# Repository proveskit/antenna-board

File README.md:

# antenna-board

This repo contains the KiCAD files for the PROVES Kit Antenna Board. This board currently goes on the +Z endcap of the satellite and hosts the antennas, interfacing ports, and some other support circuitry!

## antenna_top_cap_board_v1a
This antenna board is a reformat of the V1 Antenna Board that consolidates a bunch of the 2pos Picolock and STEMMA connectors into a single connector that runs back to the V3b EPS Board. We are probably going to leapfrog this version to land on V2 which fundementally changes things about the antenna feed path. 

## antenna_top_cap_v2
This version of the antenna top cap featuers major changes to the antenna feed path and debug passthroughs. Notable features are as follows: 
- Updated Balun Part Number (no longer sucks! still sucks to solder though)
- Addition of 12-pos and 5-pos Battery Board and Flight Controller Board debug connectors.

## antenna_top_cap_v2d
V2c plus USB charging and an SWD pass-through. See `antenna_top_cap_v2d/DECISIONS.md` for the design calls and ATP lines.
- BQ25886 2S boost charger on a new charge-only USB-C (J204), 5 V only (no PD negotiation), up to 1 A into the pack, 8.2 V float. J12 "FC USB" stays data-only.
- 1.5 A fuse plus a 0 Ohm "CHG LINK" (R210, outer face) between the charger and the battery. Hot-air R210 off before flight.
- Green LED: USB 5 V present. Red LED: charging (blinks on a fault).
- J201 (inner face) to J202 (outer face) JST-SH SWD pass-through, same pinout as the FC's J22.

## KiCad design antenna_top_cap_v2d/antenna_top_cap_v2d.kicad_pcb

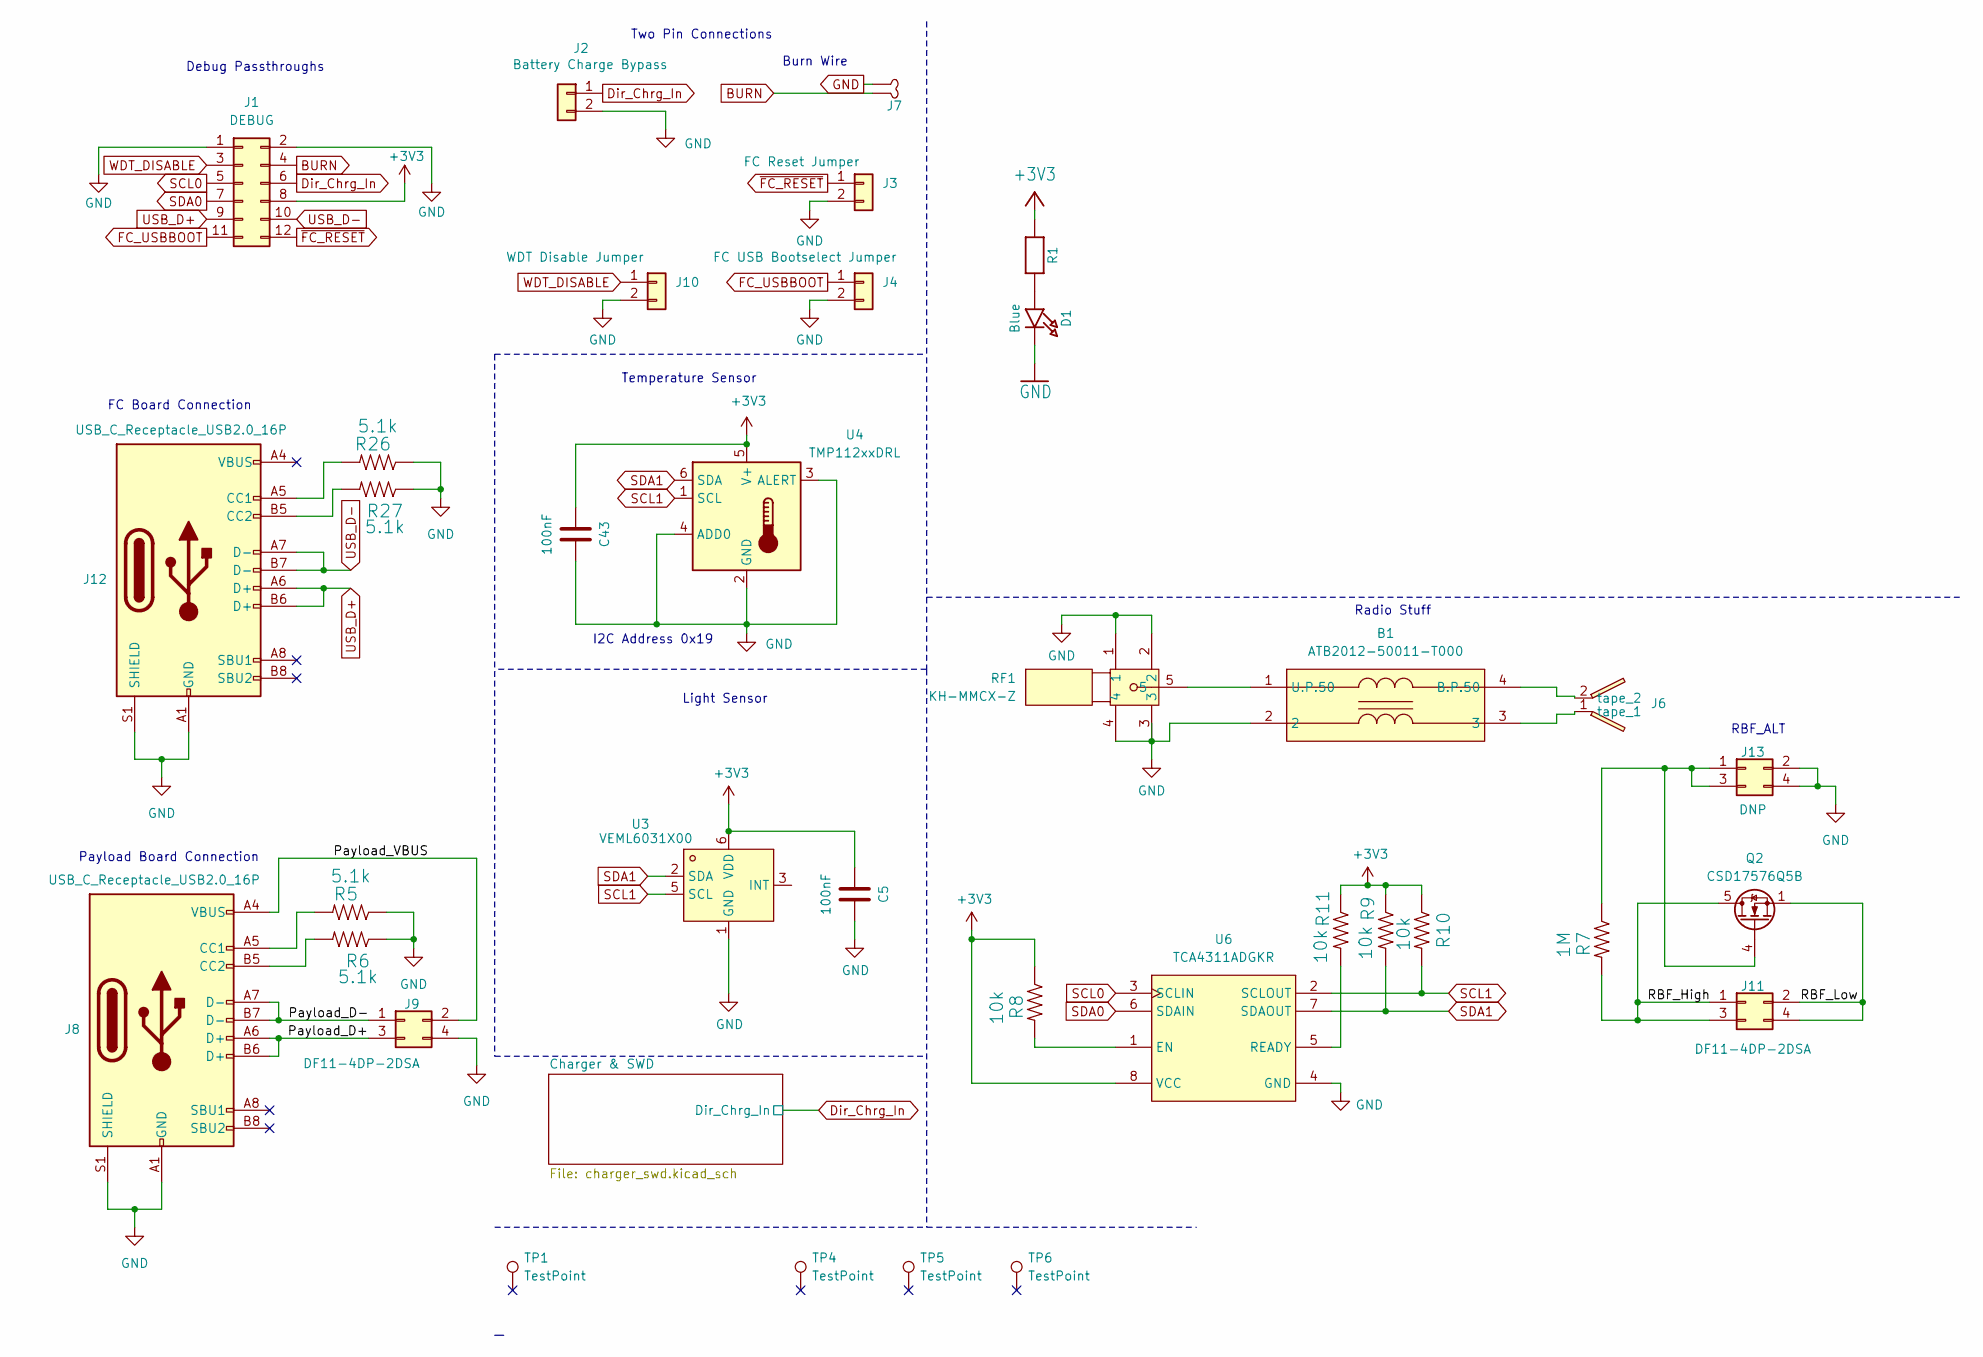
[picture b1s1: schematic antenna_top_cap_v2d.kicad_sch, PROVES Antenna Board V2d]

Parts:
B1: ATB2012-50011-T000; XFMR-SMD_ATB2012-50011-T000; LCSC Part C92015
C5, C43: 100nF; C_0805_2012Metric
D1: Blue; LED_0603_1608Metric
J1: DEBUG; Hirose_DF11-12DP-2DSA_2x06_P2.00mm_Vertical
J2: Battery Charge Bypass; PinHeader_1x02_P2.54mm_Vertical
J3: FC Reset Jumper; PinHeader_1x02_P2.54mm_Vertical
J4: FC USB Bootselect Jumper; PinHeader_1x02_P2.54mm_Vertical
J6: Tape_Measure_Antenna
J7: Burn_Wire
J8, J12: USB_C_Receptacle_USB2.0_16P; USB_C_Receptacle_HRO_TYPE-C-31-M-12
J9, J11: DF11-4DP-2DSA; Hirose_DF11-4DP-2DSA_2x02_P2.00mm_Vertical
J10: WDT Disable Jumper; PinHeader_1x02_P2.54mm_Vertical
J13: DNP; Hirose_DF11-4DP-2DSA_2x02_P2.00mm_Vertical
Q2: CSD17576Q5B; TDSON-8-1
R1: 10k; R_0402_1005Metric
R5, R6, R26, R27: 5.1k; R_0603_1608Metric
R7: 1M; R_0603_1608Metric
R8, R9, R10, R11: 10k; R_0603_1608Metric
RF1: KH-MMCX-Z; MMCX-TH_KH-MMCX-Z; LCSC Part C530664
TP1, TP4, TP5, TP6: TestPoint; MountingHole_2.7mm_M2.5_Pad
U3: VEML6031X00; SENSOR-SMD_VEML6031X00; LCSC Part C3678616
U4: TMP112xxDRL; SOT-563
U6: TCA4311ADGKR; MSOP-8_L3.0-W3.0-P0.65-LS5.0-BL; LCSC Part C130025

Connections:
+3V3: C5.1, C43.1, J1.8, R1.1, R8.1, R9.1, R10.1, R11.1, U3.6 (VDD), U4.5 (V+), U6.8 (VCC)
/Payload_D+: J8.A6 (D+), J8.B6 (D+), J9.3
/Payload_D-: J8.A7 (D-), J8.B7 (D-), J9.1
/Payload_VBUS: J8.A4 (VBUS), J8.A9 (VBUS), J8.B4 (VBUS), J8.B9 (VBUS), J9.2
/RBF_High: J11.1, J11.3, Q2.5 (D), R7.2
/RBF_Low: J11.2, J11.4, Q2.1 (S), Q2.2 (S), Q2.3 (S)
BURN: J1.4, J7.1 (Power)
Dir_Chrg_In: J1.6, J2.1; also elsewhere on the board
FC_USBBOOT: J1.11, J4.1
GND: B1.2, C5.2, C43.2, D1.2 (C), J1.1, J1.2, J2.2, J3.2, J4.2, J7.2 (GND), J8.A1 (GND), J8.A12 (GND), J8.B1 (GND), J8.B12 (GND), J8.S1 (SHIELD), J9.4, J10.2, J12.A1 (GND), J12.A12 (GND), J12.B1 (GND), J12.B12 (GND), J12.S1 (SHIELD), J13.2, J13.4, R5.1, R6.1, R26.1, R27.1, RF1.1, RF1.2, RF1.3, RF1.4, U3.1 (GND), U3.4 (GND), U4.2 (GND), U4.3 (ALERT), U4.4 (ADD0), U6.4 (GND); also elsewhere on the board
unnamed: B1.4 (B.P.50), J6.2 (tape)
unnamed: B1.1 (U.P.50), RF1.5
unnamed: D1.1 (A), R1.2
unnamed: B1.3, J6.1 (tape)
unnamed: J8.A5 (CC1), R5.2
unnamed: J8.B5 (CC2), R6.2
unnamed: J12.A5 (CC1), R26.2
unnamed: J12.B5 (CC2), R27.2
unnamed: J13.1, J13.3, Q2.4 (G), R7.1
unnamed: R8.2, U6.1 (EN)
unnamed: R11.2, U6.5 (READY)
SCL0: J1.5, U6.3 (SCLIN)
SCL1: R10.2, U3.5 (SCL), U4.1 (SCL), U6.2 (SCLOUT)
SDA0: J1.7, U6.6 (SDAIN)
SDA1: R9.2, U3.2 (SDA), U4.6 (SDA), U6.7 (SDAOUT)
USB_D+: J1.9, J12.A6 (D+), J12.B6 (D+)
USB_D-: J1.10, J12.A7 (D-), J12.B7 (D-)
WDT_DISABLE: J1.3, J10.1
~FC_RESET: J1.12, J3.1

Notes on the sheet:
Light Sensor
Two Pin Connections
I2C Address 0x19
Radio Stuff
Debug Passthroughs
FC Board Connection
RBF_ALT
Payload Board Connection
Burn Wire
Temperature Sensor

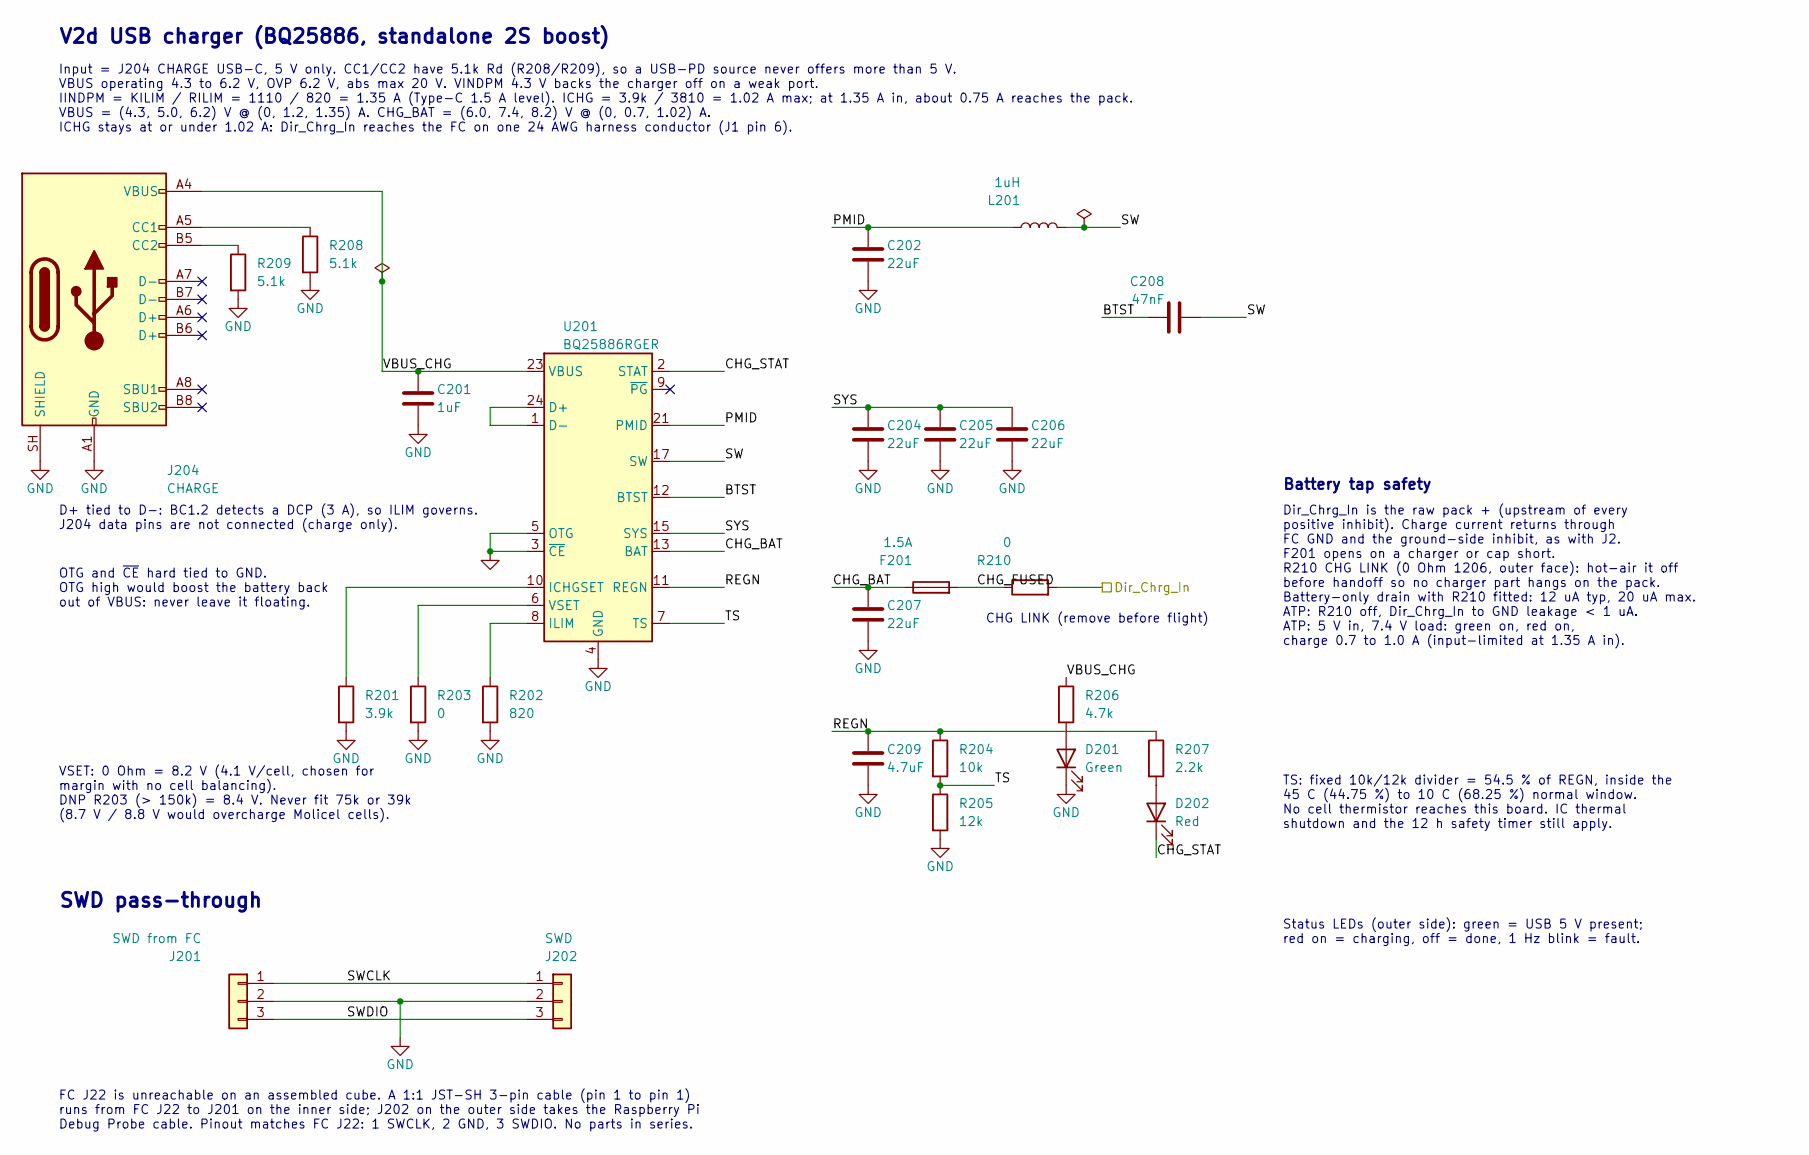
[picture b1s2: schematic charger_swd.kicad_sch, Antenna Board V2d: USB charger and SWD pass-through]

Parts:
C201: 1uF; C_0603_1608Metric; LCSC C15849
C202: 22uF; C_0805_2012Metric; LCSC C45783
C204, C205, C206, C207: 22uF; C_1206_3216Metric; LCSC C12891
C208: 47nF; C_0603_1608Metric; LCSC C1622
C209: 4.7uF; C_0603_1608Metric; LCSC C19666
D201: Green; LED_0805_2012Metric; LCSC C2297
D202: Red; LED_0603_1608Metric; LCSC C2286
F201: 1.5A; Fuse_1206_3216Metric; MPN 046601.5NRHF; LCSC C187598
J201: SWD from FC; JST_SH_BM03B-SRSS-TB_1x03-1MP_P1.00mm_Vertical; MPN BM03B-SRSS-TB(LF)(SN); LCSC C160389
J202: SWD; JST_SH_BM03B-SRSS-TB_1x03-1MP_P1.00mm_Vertical; MPN BM03B-SRSS-TB(LF)(SN); LCSC C160389
J204: CHARGE; USB_C_Receptacle_HRO_TYPE-C-31-M-12; MPN TYPE-C-31-M-12; LCSC C165948
L201: 1uH; L_Changjiang_FNR4030S; MPN FNR4030S1R0MT; LCSC C167865
R201: 3.9k; R_0402_1005Metric; LCSC C51721
R202: 820; R_0402_1005Metric; LCSC C25135
R203: 0; R_0402_1005Metric; LCSC C17168
R204: 10k; R_0402_1005Metric; LCSC C25744
R205: 12k; R_0402_1005Metric; LCSC C25752
R206: 4.7k; R_0603_1608Metric; LCSC C23162
R207: 2.2k; R_0603_1608Metric; LCSC C4190
R208, R209: 5.1k; R_0603_1608Metric; LCSC C23186
R210: 0; R_1206_3216Metric; LCSC C17888
U201: BQ25886RGER; Texas_RGE0024H_VQFN-24-1EP_4x4mm_P0.5mm_EP2.7x2.7mm; LCSC C2765094

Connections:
/Charger & SWD/BTST: C208.1, U201.12 (BTST)
/Charger & SWD/CHG_BAT: C207.1, F201.1, U201.13 (BAT), U201.14 (BAT)
/Charger & SWD/CHG_FUSED: F201.2, R210.1
/Charger & SWD/CHG_STAT: D202.1 (K), U201.2 (STAT)
/Charger & SWD/PMID: C202.1, L201.1, U201.21 (PMID), U201.22 (PMID)
/Charger & SWD/REGN: C209.1, R204.1, R207.1, U201.11 (REGN)
/Charger & SWD/SW: C208.2, L201.2, U201.17 (SW), U201.18 (SW)
/Charger & SWD/SWCLK: J201.1, J202.1
/Charger & SWD/SWDIO: J201.3, J202.3
/Charger & SWD/SYS: C204.1, C205.1, C206.1, U201.15 (SYS), U201.16 (SYS)
/Charger & SWD/TS: R204.2, R205.1, U201.7 (TS)
/Charger & SWD/VBUS_CHG: C201.1, J204.A4 (VBUS), J204.A9 (VBUS), J204.B4 (VBUS), J204.B9 (VBUS), R206.1, U201.23 (VBUS)
Dir_Chrg_In: R210.2; also elsewhere on the board
GND: C201.2, C202.2, C204.2, C205.2, C206.2, C207.2, C209.2, D201.1 (K), J201.2, J202.2, J204.A1 (GND), J204.A12 (GND), J204.B1 (GND), J204.B12 (GND), J204.SH (SHIELD), R201.2, R202.2, R203.2, R205.2, R208.2, R209.2, U201.3 (~CE), U201.4 (GND), U201.5 (OTG), U201.19 (GND), U201.20 (GND), U201.25 (GND); also elsewhere on the board
unnamed: D201.2 (A), R206.2
unnamed: D202.2 (A), R207.2
unnamed: J204.A5 (CC1), R208.1
unnamed: J204.B5 (CC2), R209.1
unnamed: U201.1 (D-), U201.24 (D+)
unnamed: R201.1, U201.10 (ICHGSET)
unnamed: R202.1, U201.8 (ILIM)
unnamed: R203.1, U201.6 (VSET)

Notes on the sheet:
CHG LINK (remove before flight)
V2d USB charger (BQ25886, standalone 2S boost)
Input = J204 CHARGE USB-C, 5 V only. CC1/CC2 have 5.1k Rd (R208/R209), so a USB-PD source never offers more than 5 V. VBUS operating 4.3 to 6.2 V, OVP 6.2 V, abs max 20 V. VINDPM 4.3 V backs the charger off on a weak port. IINDPM = KILIM / RILIM = 1110 / 820 = 1.35 A (Type-C 1.5 A level). ICHG = 3.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
D+ tied to D-: BC1.2 detects a DCP (3 A), so ILIM governs. J204 data pins are not connected (charge only).
OTG and ~{CE} hard tied to GND. OTG high would boost the battery back out of VBUS: never leave it floating.
VSET: 0 Ohm = 8.2 V (4.1 V/cell, chosen for margin with no cell balancing). DNP R203 (> 150k) = 8.4 V. Never fit 75k or 39k (8.7 V / 8.8 V would overcharge Molicel cells).
TS: fixed 10k/12k divider = 54.5 % of REGN, inside the 45 C (44.75 %) to 10 C (68.25 %) normal window. No cell thermistor reaches this board. IC thermal shutdown and the 12 h safety timer still apply.
Battery tap safety
Dir_Chrg_In is the raw pack + (upstream of every positive inhibit). Charge current returns through FC GND and the ground-side inhibit, as with J2. F201 opens on a charger or cap short. R210 CHG LINK (0 Ohm 1206, outer face): hot-air it off before handoff so no charger part hangs on the pack. Batter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
Status LEDs (outer side): green = USB 5 V present; red on = charging, off = done, 1 Hz blink = fault.
SWD pass-through
FC J22 is unreachable on an assembled cube. A 1:1 JST-SH 3-pin cable (pin 1 to pin 1) runs from FC J22 to J201 on the inner side; J202 on the outer side takes the Raspberry Pi Debug Probe cable. Pinout matches FC J22: 1 SWCLK, 2 GND, 3 SWDIO. No parts in series.

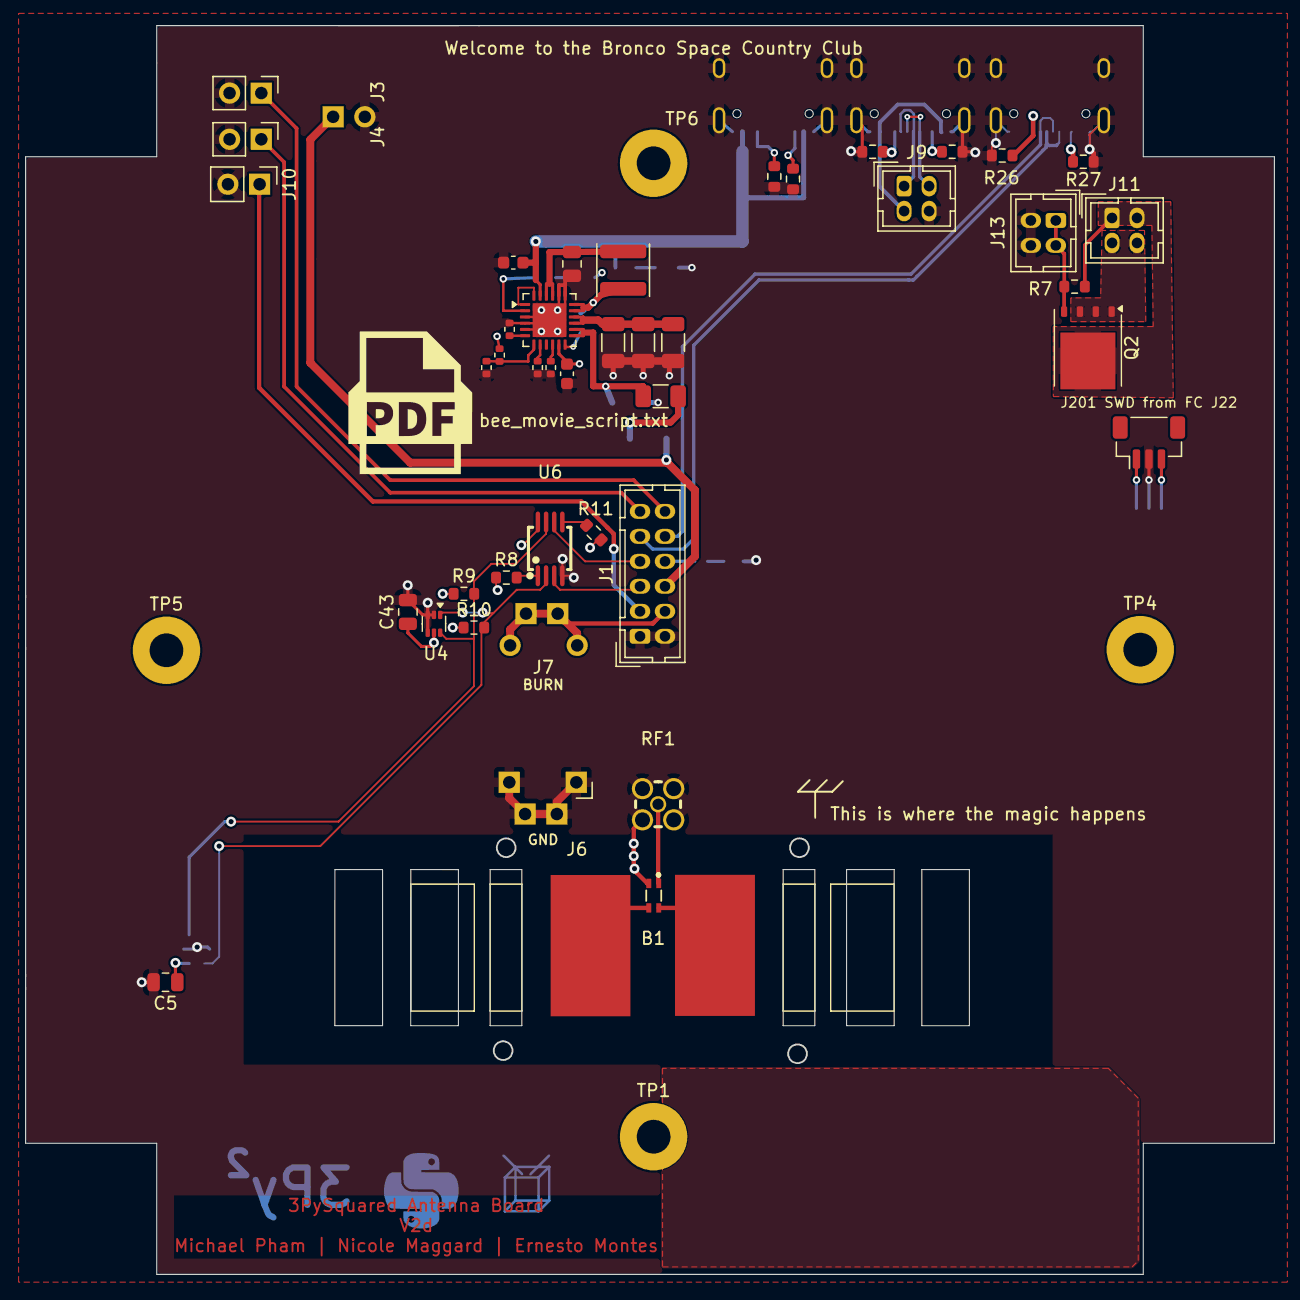
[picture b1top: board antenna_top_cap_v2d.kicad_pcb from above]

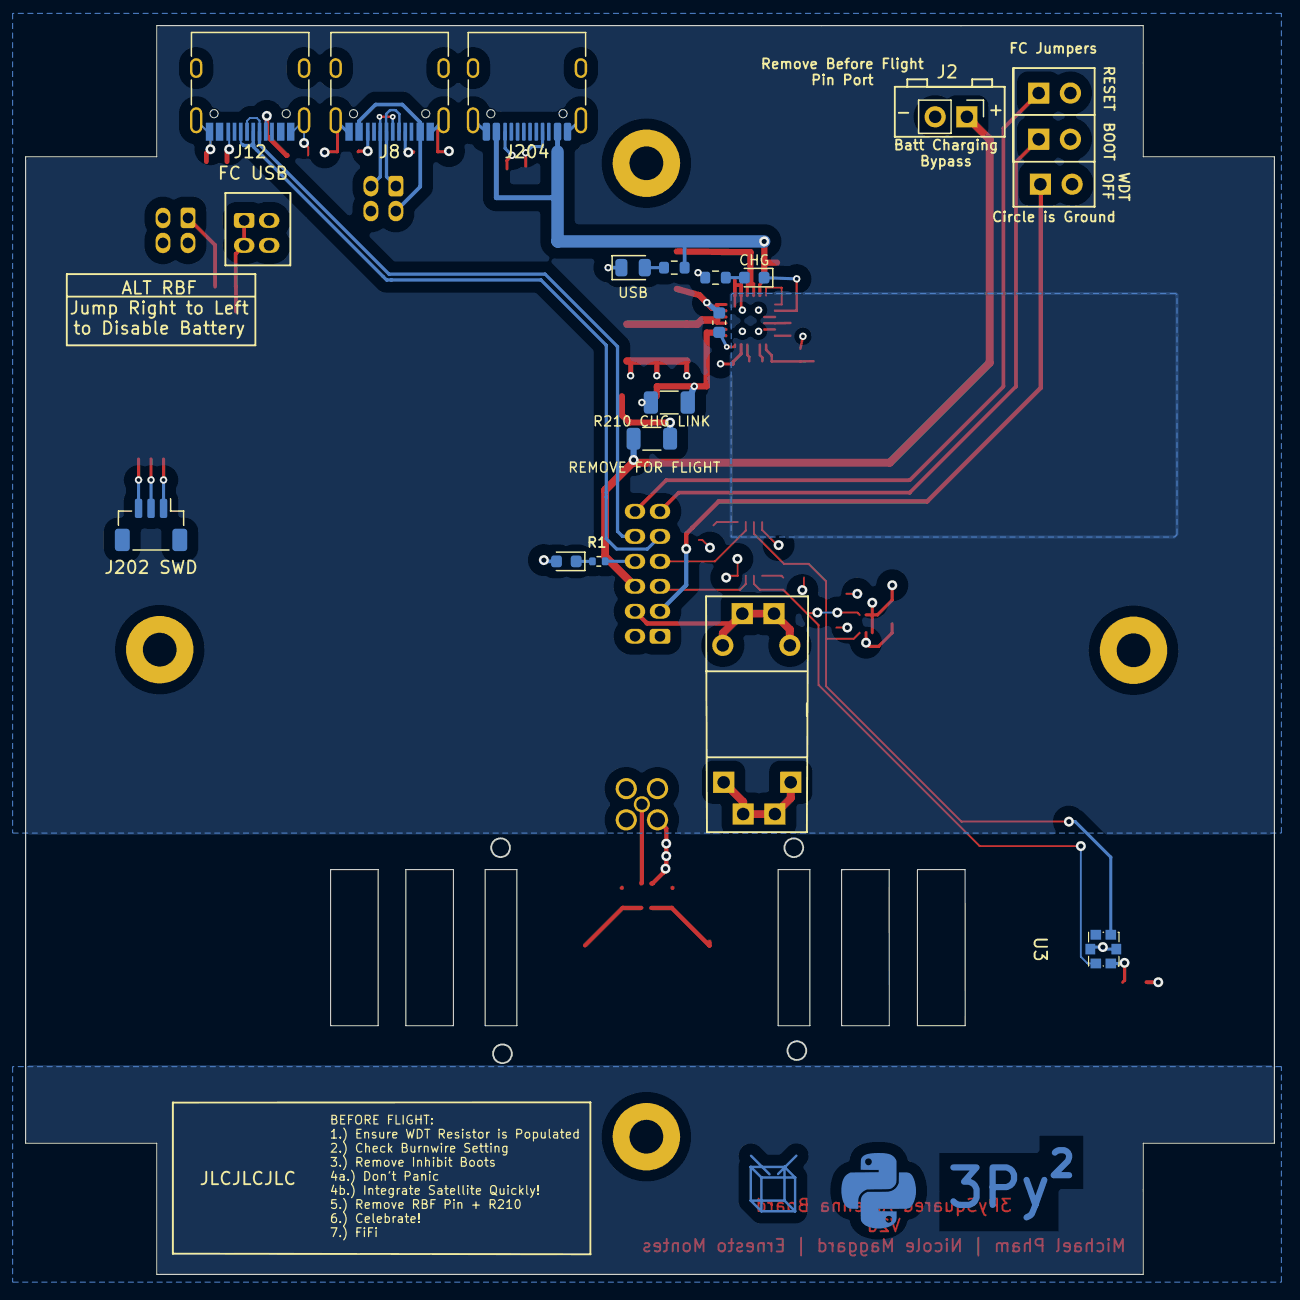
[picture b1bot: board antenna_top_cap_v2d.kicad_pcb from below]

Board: 4 copper layers, 100.0 x 100.0 mm, 61 parts (15 on the bottom side), 49 nets.

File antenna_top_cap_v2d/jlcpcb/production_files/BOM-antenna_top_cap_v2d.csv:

Comment,Designator,Footprint,LCSC,Quantity
ATB2012-50011-T000,B1,XFMR-SMD_ATB2012-50011-T000,C92015,1
1uF,C201,C_0603_1608Metric,C15849,1
22uF,C202,C_0805_2012Metric,C45783,1
22uF,"C204,C205,C206,C207",C_1206_3216Metric,C12891,4
47nF,C208,C_0603_1608Metric,C1622,1
4.7uF,C209,C_0603_1608Metric,C19666,1
100nF,"C43,C5",C_0805_2012Metric,C28233,2
Blue,D1,LED_0603_1608Metric,C2288,1
Green,D201,LED_0805_2012Metric,C2297,1
Red,D202,LED_0603_1608Metric,C2286,1
1.5A,F201,Fuse_1206_3216Metric,C187598,1
DEBUG,J1,Hirose_DF11-12DP-2DSA_2x06_P2.00mm_Vertical,C506658,1
DF11-4DP-2DSA,"J11,J9",Hirose_DF11-4DP-2DSA_2x02_P2.00mm_Vertical,C506665,2
USB_C_Receptacle_USB2.0_16P,"J12,J204,J8",USB_C_Receptacle_HRO_TYPE-C-31-M-12,C165948,3
DNP,J13,Hirose_DF11-4DP-2DSA_2x02_P2.00mm_Vertical,,1
SWD from FC,"J201,J202",JST_SH_BM03B-SRSS-TB_1x03-1MP_P1.00mm_Vertical,C160389,2
1uH,L201,L_Changjiang_FNR4030S,C167865,1
CSD17576Q5B,Q2,TDSON-8-1,C2876547,1
10k,"R1,R204",R_0402_1005Metric,C25744,2
10k,"R10,R11,R8,R9",R_0603_1608Metric,C25804,4
3.9k,R201,R_0402_1005Metric,C51721,1
820,R202,R_0402_1005Metric,C25135,1
0,R203,R_0402_1005Metric,C17168,1
12k,R205,R_0402_1005Metric,C25752,1
4.7k,R206,R_0603_1608Metric,C23162,1
2.2k,R207,R_0603_1608Metric,C4190,1
5.1k,"R208,R209,R26,R27,R5,R6",R_0603_1608Metric,C23186,6
0,R210,R_1206_3216Metric,C17888,1
1M,R7,R_0603_1608Metric,C22935,1
KH-MMCX-Z,RF1,MMCX-TH_KH-MMCX-Z,C530664,1
BQ25886RGER,U201,Texas_RGE0024H_VQFN-24-1EP_4x4mm_P0.5mm_EP2.7x2.7mm,C2765094,1
VEML6031X00,U3,SENSOR-SMD_VEML6031X00,C3678616,1
TMP112xxDRL,U4,SOT-563,C3019122,1
TCA4311ADGKR,U6,MSOP-8_L3.0-W3.0-P0.65-LS5.0-BL,C130025,1

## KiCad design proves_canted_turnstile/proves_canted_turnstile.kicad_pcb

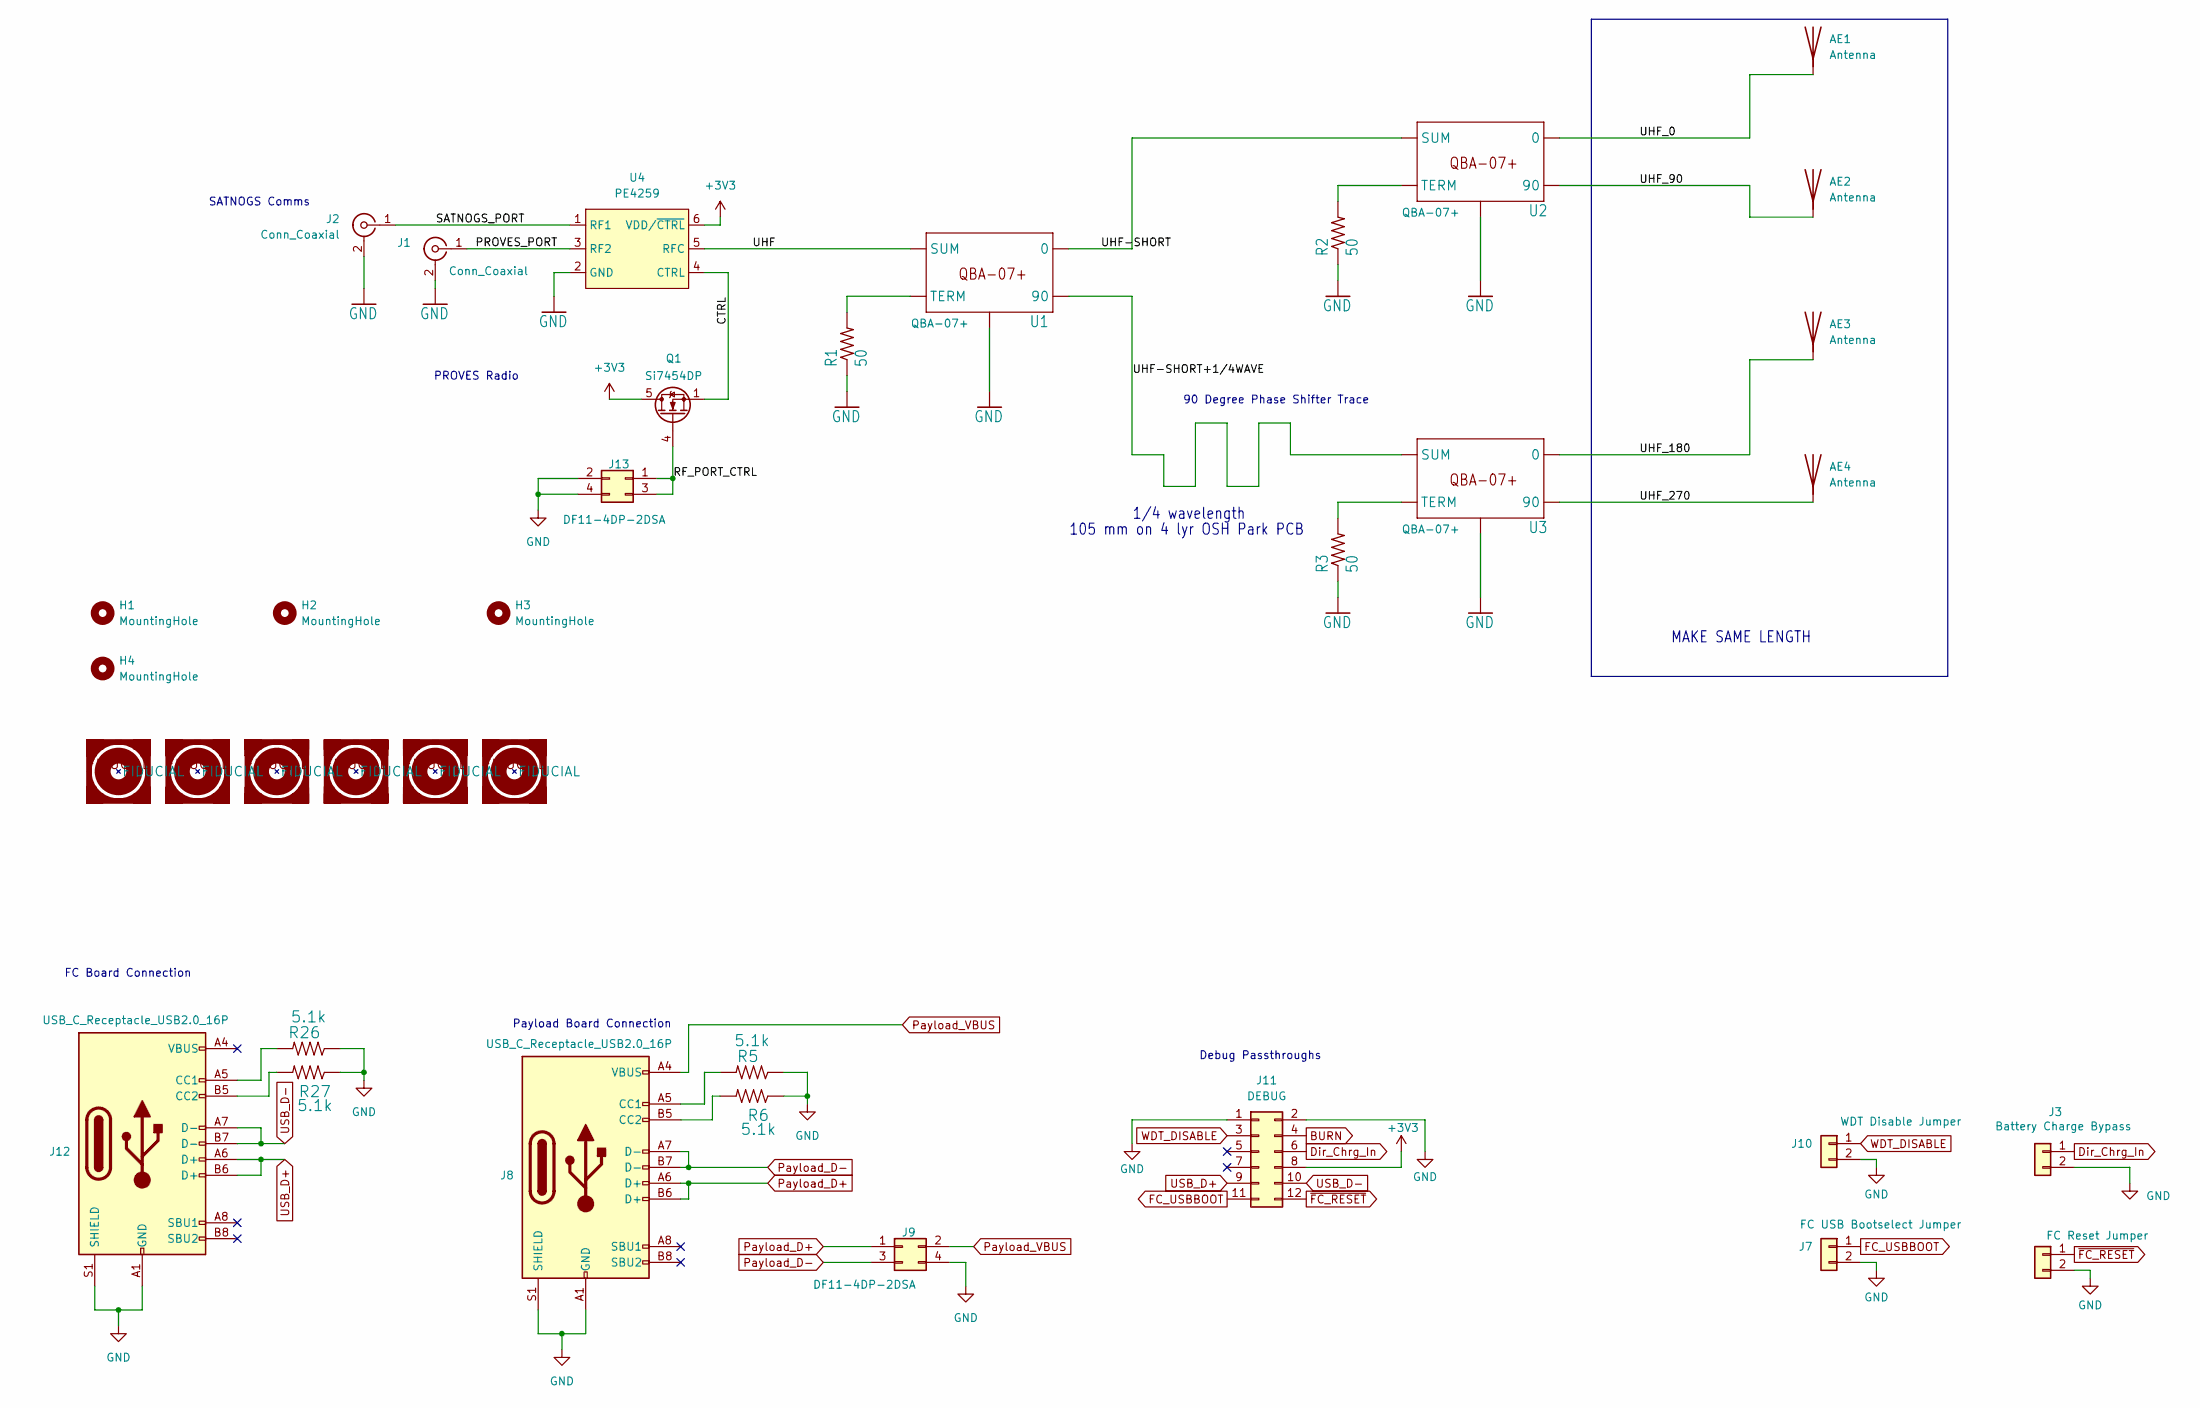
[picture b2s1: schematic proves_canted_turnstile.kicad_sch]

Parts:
AE1, AE2, AE3, AE4: Antenna; Singular Tape Measure
FIDUCIAL1, FIDUCIAL2, FIDUCIAL3, FIDUCIAL4, FIDUCIAL6, FIDUCIAL7: FIDUCIAL-1.0X2.0
H1, H2, H3, H4: MountingHole; MountingHole_2.7mm_M2.5_Pad
J1, J2: Conn_Coaxial; MMCX_Molex_73415-1471_Vertical
J3: Battery Charge Bypass; PinHeader_1x02_P2.54mm_Vertical
J6: FC Reset Jumper; PinHeader_1x02_P2.54mm_Vertical
J7: FC USB Bootselect Jumper; PinHeader_1x02_P2.54mm_Vertical
J8, J12: USB_C_Receptacle_USB2.0_16P; USB_C_Receptacle_HRO_TYPE-C-31-M-12
J9, J13: DF11-4DP-2DSA; Hirose_DF11-4DP-2DSA_2x02_P2.00mm_Vertical
J10: WDT Disable Jumper; PinHeader_1x02_P2.54mm_Vertical
J11: DEBUG; Hirose_DF11-12DP-2DSA_2x06_P2.00mm_Vertical
Q1: Si7454DP; PowerPAK_SO-8_Single
R1, R2, R3: 50; .0603-C-NOSILK
R5, R6, R26, R27: 5.1k; R_0603_1608Metric
U1, U2, U3: QBA-07+
U4: PE4259; SOT-363_SC-70-6_Handsoldering

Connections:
+3V3: J11.8, Q1.5 (D), U4.6 (VDD/~CTRL)
/CTRL: Q1.1 (S), Q1.2 (S), Q1.3 (S), U4.4 (CTRL)
/PROVES_PORT: J1.1 (In), U4.3 (RF2)
/RF_PORT_CTRL: J13.1, J13.3, Q1.4 (G)
/SATNOGS_PORT: J2.1 (In), U4.1 (RF1)
/UHF: U1.1 (SUM), U4.5 (RFC)
/UHF-SHORT: U1.6 (0), U2.1 (SUM)
/UHF-SHORT+1/4WAVE: U1.10 (90), U3.1 (SUM)
/UHF_0: AE1.1 (A), U2.6 (0)
/UHF_90: AE2.1 (A), U2.10 (90)
/UHF_180: AE3.1 (A), U3.6 (0)
/UHF_270: AE4.1 (A), U3.10 (90)
BURN: J11.4
Dir_Chrg_In: J3.1, J11.6
FC_USBBOOT: J7.1, J11.11
GND: J1.2 (Ext), J2.2 (Ext), J3.2, J6.2, J7.2, J8.A1 (GND), J8.A12 (GND), J8.B1 (GND), J8.B12 (GND), J8.S1 (SHIELD), J9.4, J10.2, J11.1, J11.2, J12.A1 (GND), J12.A12 (GND), J12.B1 (GND), J12.B12 (GND), J12.S1 (SHIELD), J13.2, J13.4, R1.1, R2.1, R3.1, R5.1, R6.1, R26.1, R27.1, U1.2 (GND), U1.3 (GND), U1.4 (GND), U1.7 (GND), U1.8 (GND), U1.9 (GND), U1.GND-NO-PAD (GND), U2.2 (GND), U2.3 (GND), U2.4 (GND), U2.7 (GND), U2.8 (GND), U2.9 (GND), U2.GND-NO-PAD (GND), U3.2 (GND), U3.3 (GND), U3.4 (GND), U3.7 (GND), U3.8 (GND), U3.9 (GND), U3.GND-NO-PAD (GND), U4.2 (GND)
unnamed: J8.A5 (CC1), R5.2
unnamed: J8.B5 (CC2), R6.2
unnamed: J12.A5 (CC1), R26.2
unnamed: J12.B5 (CC2), R27.2
unnamed: R1.2, U1.5 (TERM)
unnamed: R2.2, U2.5 (TERM)
unnamed: R3.2, U3.5 (TERM)
Payload_D+: J8.A6 (D+), J8.B6 (D+), J9.1
Payload_D-: J8.A7 (D-), J8.B7 (D-), J9.3
Payload_VBUS: J8.A4 (VBUS), J8.A9 (VBUS), J8.B4 (VBUS), J8.B9 (VBUS), J9.2
USB_D+: J11.9, J12.A6 (D+), J12.B6 (D+)
USB_D-: J11.10, J12.A7 (D-), J12.B7 (D-)
WDT_DISABLE: J10.1, J11.3
~FC_RESET: J6.1, J11.12

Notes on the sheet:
PROVES Radio
MAKE SAME LENGTH
Debug Passthroughs
SATNOGS Comms
90 Degree Phase Shifter Trace
FC Board Connection
1/4 wavelength
105 mm on 4 lyr OSH Park PCB
Payload Board Connection

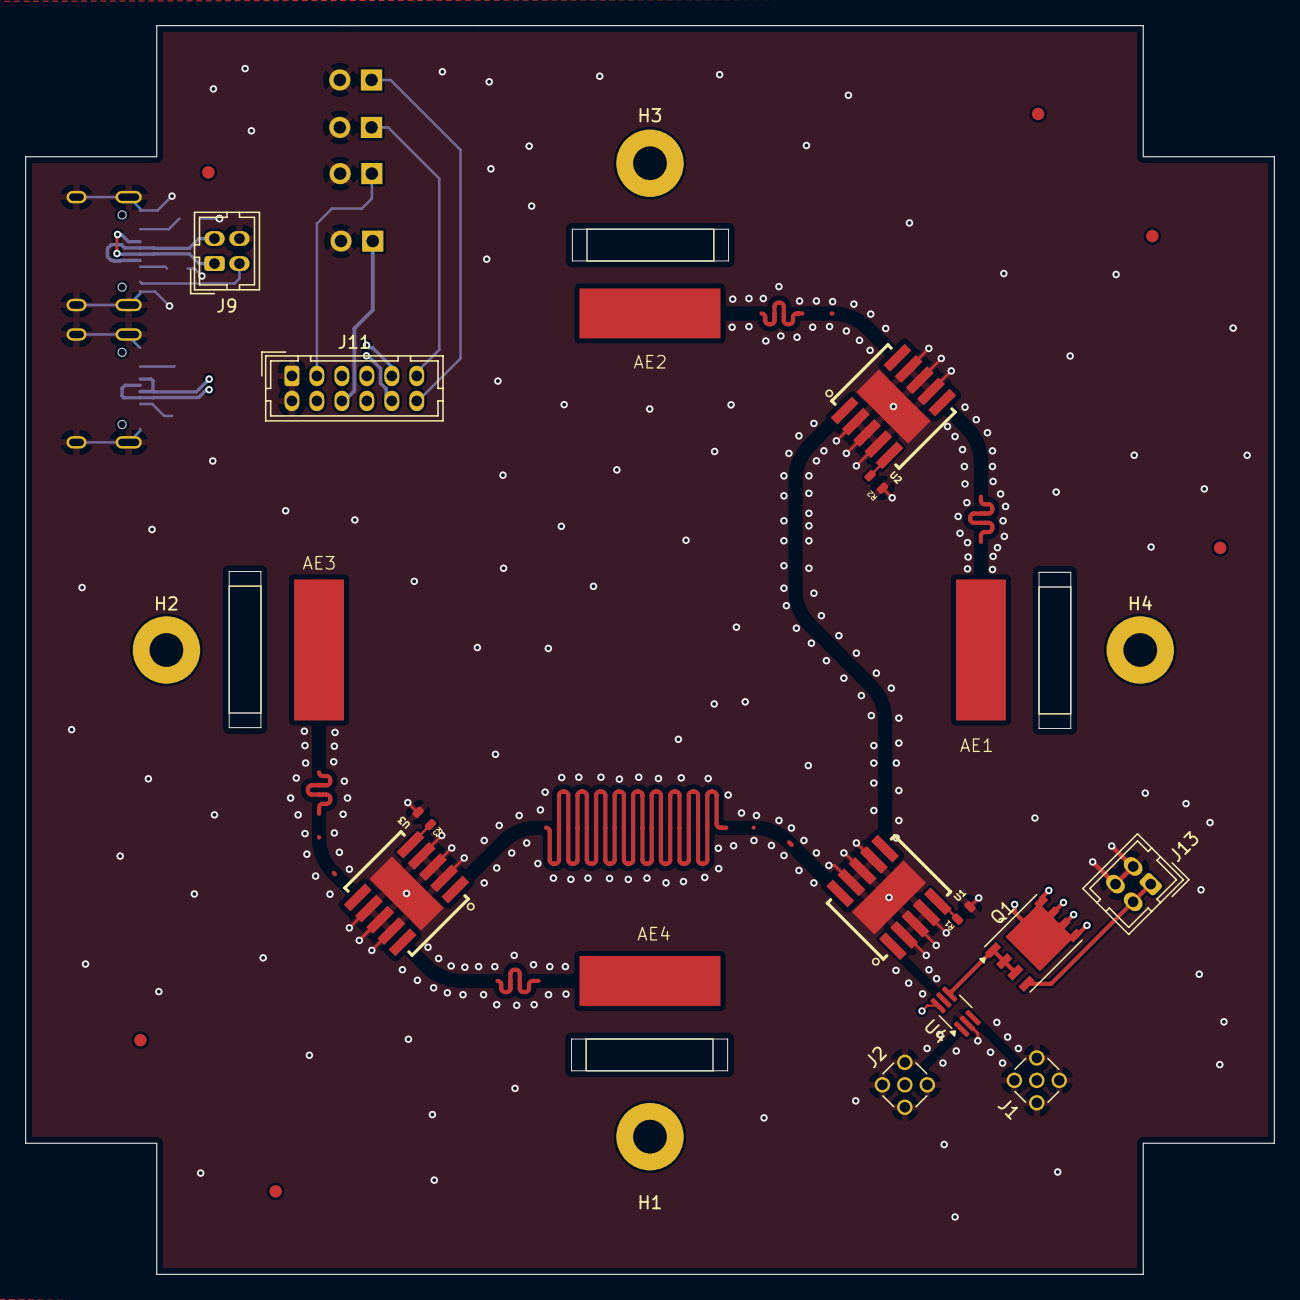
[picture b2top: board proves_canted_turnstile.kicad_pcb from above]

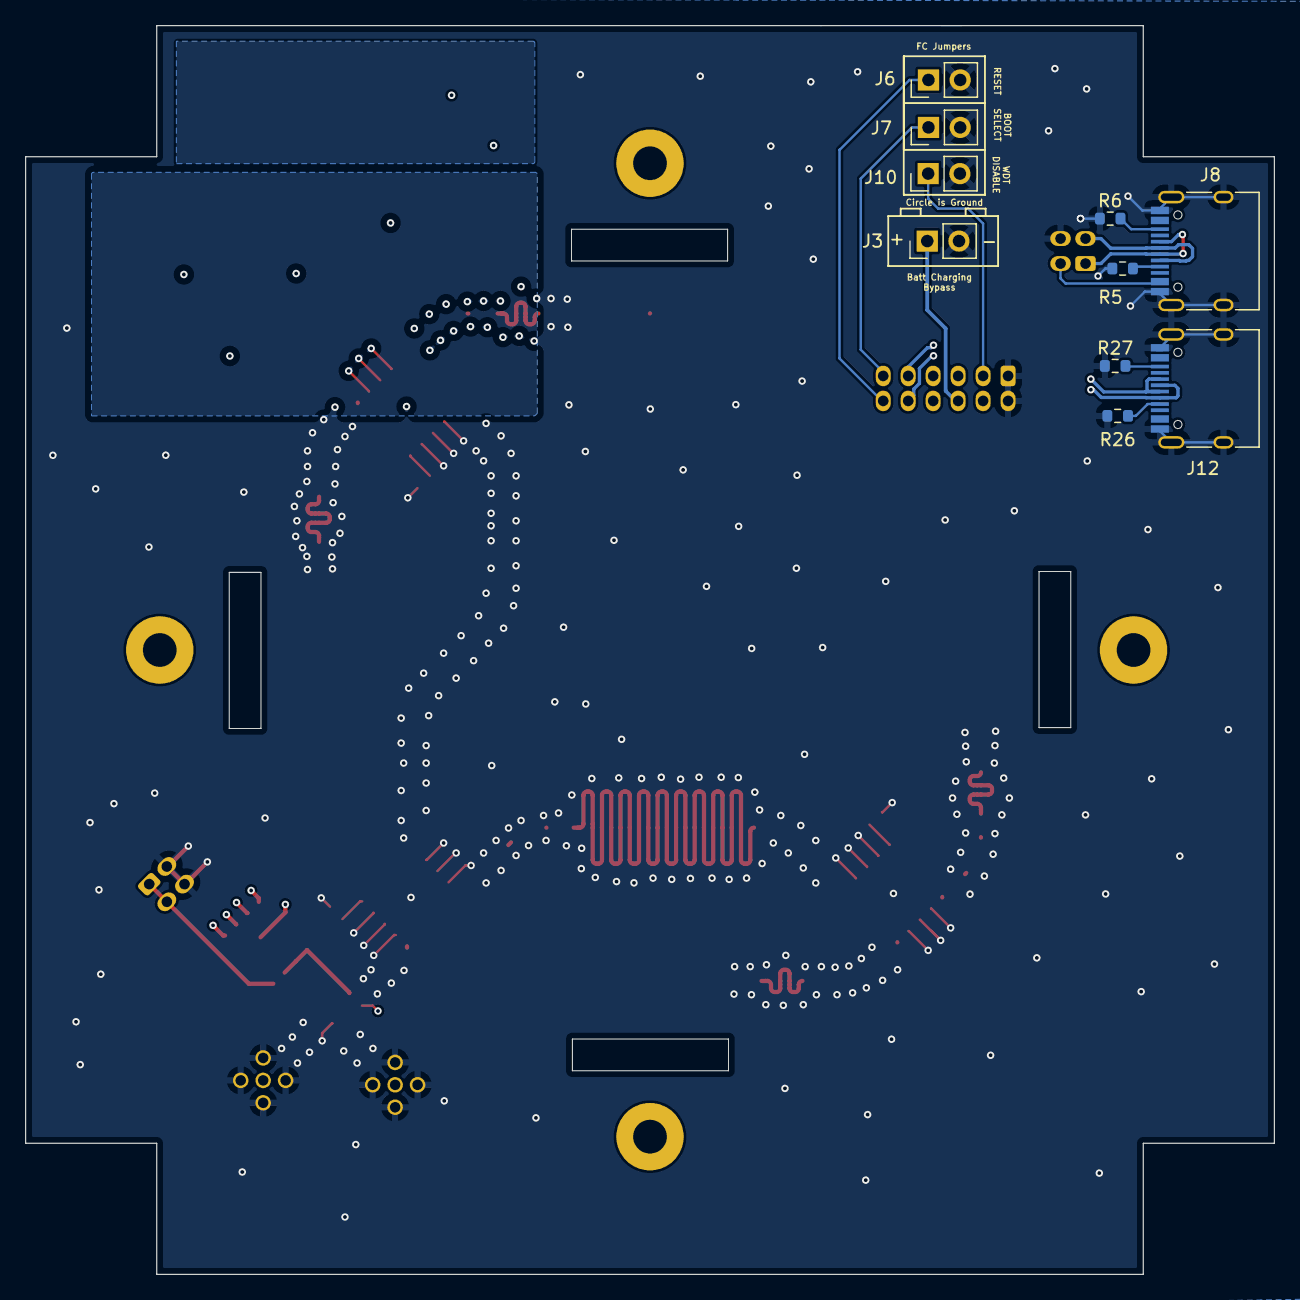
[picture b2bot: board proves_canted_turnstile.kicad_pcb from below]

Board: 4 copper layers, 100.0 x 100.0 mm, 37 parts (10 on the bottom side), 29 nets.
